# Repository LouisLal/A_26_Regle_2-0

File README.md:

# C3I A26_Règle_PCB

Compétition de Conception de Circuits Imprimés – Université de Sherbrooke, Automne 2026

## Thème : Règle PCB

Bienvenue à la compétition de conception de PCB de l’Université de Sherbrooke, édition Automne 2026!
Cette compétition a pour but d'agir comme une introduction au monde de la conception de circuit imprimé (PCB). Le thème simple de cette compétition invite les participants à expérimenter, à découvrir et à essayer quelque chose de nouveau. Votre but sera de faire un PCB qui prendra la forme d'une règle tout en ayant un circuit fonctionnel.

---

## Déroulement

Voici l'ensemble des dates importantes de la session, réparties entre les événements et les dates de commandes :

### Calendrier des événements et ateliers

* **9 septembre 2026 (17h00)** : Présentation du projet C3I A26 + Atelier de soudure THT
* **16 septembre 2026 (17h00)** : Atelier de soudure THT + Atelier d'intro à l'électronique
* **23 septembre 2026 (17h00)** : Atelier introduction à KiCad
* **30 septembre 2026 (17h00)** : Atelier Kicad - PCB
* **7 octobre 2026 (17h00)** : Séminaire - Introduction MCU
* **14 octobre 2026 (17h00)** : Séminaires sur les normes de conception électroniques (Schémas + PCB)
* **21 octobre 2026 (17h00)** : Séminaire sur les protocoles de communications
* **28 octobre 2026 (17h00)** : Atelier - Un projet sans devboards
* **4 novembre 2026 (17h00)** : Atelier de soudure (THT + SMD)
* **11 novembre 2026 (17h00)** : Période de travail et d'échange (validation par les pairs)
* **18 novembre 2026 (17h00)** : Séminaire - Intro AmpliOp
* **25 novembre 2026 (17h00)** : Atelier - MicroPython
* **2 décembre 2026 (17h00)** : Séminaire - Assemblage automatique
* **9 décembre 2026 (17h00)** : Période de travail et d'échange (validation par les pairs)
* **16 décembre 2026 (17h00)** : Période de travail et d'échange (validation par les pairs)

### Dates de commande (Pièces et PCB)

* **9 septembre 2026** : Début de la compétition
* **2 octobre 2026** : C3I - Commande de pièces ou PCB
* **16 octobre 2026** : C3I - Commande de pièces ou PCB et fin des inscriptions
* **30 octobre 2026** : C3I - Commande de pièces ou PCB
* **13 novembre 2026** : C3I - Commande de pièces ou PCB (Dernière commande LCSC)
* **27 novembre 2026** : C3I - Commande de pièces ou PCB
* **11 décembre 2026** : C3I - Commande de pièces ou PCB (Dernière commande)
* **30 décembre 2026 (23h59)** : Date limite - Remise projet C3I A26
* **4 janvier 2027 (17h30)** : Événement de compétition C3I A26 (Évaluation, présentation et remise des prix)

---

### Comment forker le dépôt

1. Accédez au dépôt GitHub officiel à l'adresse suivante : `[https://github.com/CCI-udes/A26_Regle_PCB](https://github.com/CCI-udes/A_26_Regle_2-0)`
2. Cliquez sur le bouton "Fork" en haut à droite de la page du dépôt.
3. Sélectionnez votre propre compte GitHub comme destination du fork.
4. Clonez le dépôt forké sur votre machine locale.

---

## Règlement

* Équipes de 1 à 3 personnes. **Si c'est votre première fois à faire un PCB, on vous recommande de vous mettre en équipe de 2**.
* Frais de participation : 1 e-mail à envoyer à un potentiel commanditaire par membre de l'équipe. Voir le lien suivant pour de l'aide: [Repo commandite](https://github.com/CCI-udes/documents_sponsors).
* Dimensions maximales PCB : Longueur de **15,5 cm par 3 cm maximum**.
* Les PCB ayant plus de 2 couches sont acceptés, mais la différence de prix devra être ajoutée au BOM.
* BOM maximum (produit final) : **50 $**.
* Coût de développement maximal autorisé : **100 $**.
* Utilisation de **DevBoard permise** pour le développement (pénalité de -7 points si présente dans la version finale).
* Objectif : **s’amuser et apprendre** !

---

## Remise

Chaque équipe doit fournir via son fork GitHub avant le **30 décembre 2026** :

* Schéma électrique (nettoyé et en PDF).
* Fichiers Gerber du PCB.
* Le code logiciel si applicable.
* BOM (Bill of Materials) conforme (incluant distributeurs et prix réels).
* Documentation complète du projet.

---

## Évaluation

Les projets seront notés sur un total de **250 points**, répartis de la façon suivante :

* **Idée [15 pts]** (Appréciation juges [10 pts] + Appréciation participants [5 pts])

* **Fonctionnalité [35 pts]** (Démonstration fonctionnelle [20 pts] + Compréhension des parties non-fonctionnelles [15 pts])

* **Complexité [45 pts]** (Hardware [25 pts] + Software [20 pts])

* **Gestion des ressources [25 pts]** (Bill Of Materials [20 pts] + Nombre de commandes [5 pts])

* **Démonstration [55 pts]** (Présentation orale [25 pts], Documentation écrite [20 pts], Esthétique/boîtier [10 pts])

* **Conception électronique [75 pts]** (Choix composants [10 pts], Schéma [10 pts], Qualité PCB [20 pts], Conception préventive [10 pts], Assemblage/réparation [10 pts], Qualité des soudures [15 pts])

---

## Prix

* 🏆 **Prix de conception** – Évalué sur **250 pts** (Innovation, ingéniosité, minutie et originalité dans la conception).
* ⚡ **Prix du gningnégnieur** – Évalué sur **170 pts** (Démontre une compréhension des parties non-fonctionnelles, valorise la créativité et l'apprentissage).
* 💼 **Prix du vendeur** – Évalué sur **125 pts** (Savoir organiser ses ressources, minimiser les pertes, attention au détail, esthétique et finition "best-seller").

---

## Ressources utiles

* **Microcontrôleurs recommandés** : ESP32-C3, ESP32-S3, RP2040, PB-03, CH32V003.
* **Logiciels de conception** : KiCad, Altium Designer, EasyEDA.
* **Discord** : [Lien d’invitation](https://discord.gg/xeSqf3N3Hw).

---

## Contacts

* **Jacob Turcotte** – Jacob.Turcotte@usherbrooke.ca (FAC. GÉNIE Robotique)
* **Miriam Caisse** – Miriam.Caisse@usherbrooke.ca (FAC. GÉNIE Électrique)
* **Jordan Gagnon** – Jordan.Gagnon@usherbrooke.ca (FAC. GÉNIE Électrique)
* **Alyson Bourque** - Alyson.Bourque@USherbrooke.ca (FAC. GÉNIE Électrique)
* **Céleste-Lyi Martel** - Celeste-Lyi.Martel@USherbrooke.ca (FAC. GÉNIE Robotique)

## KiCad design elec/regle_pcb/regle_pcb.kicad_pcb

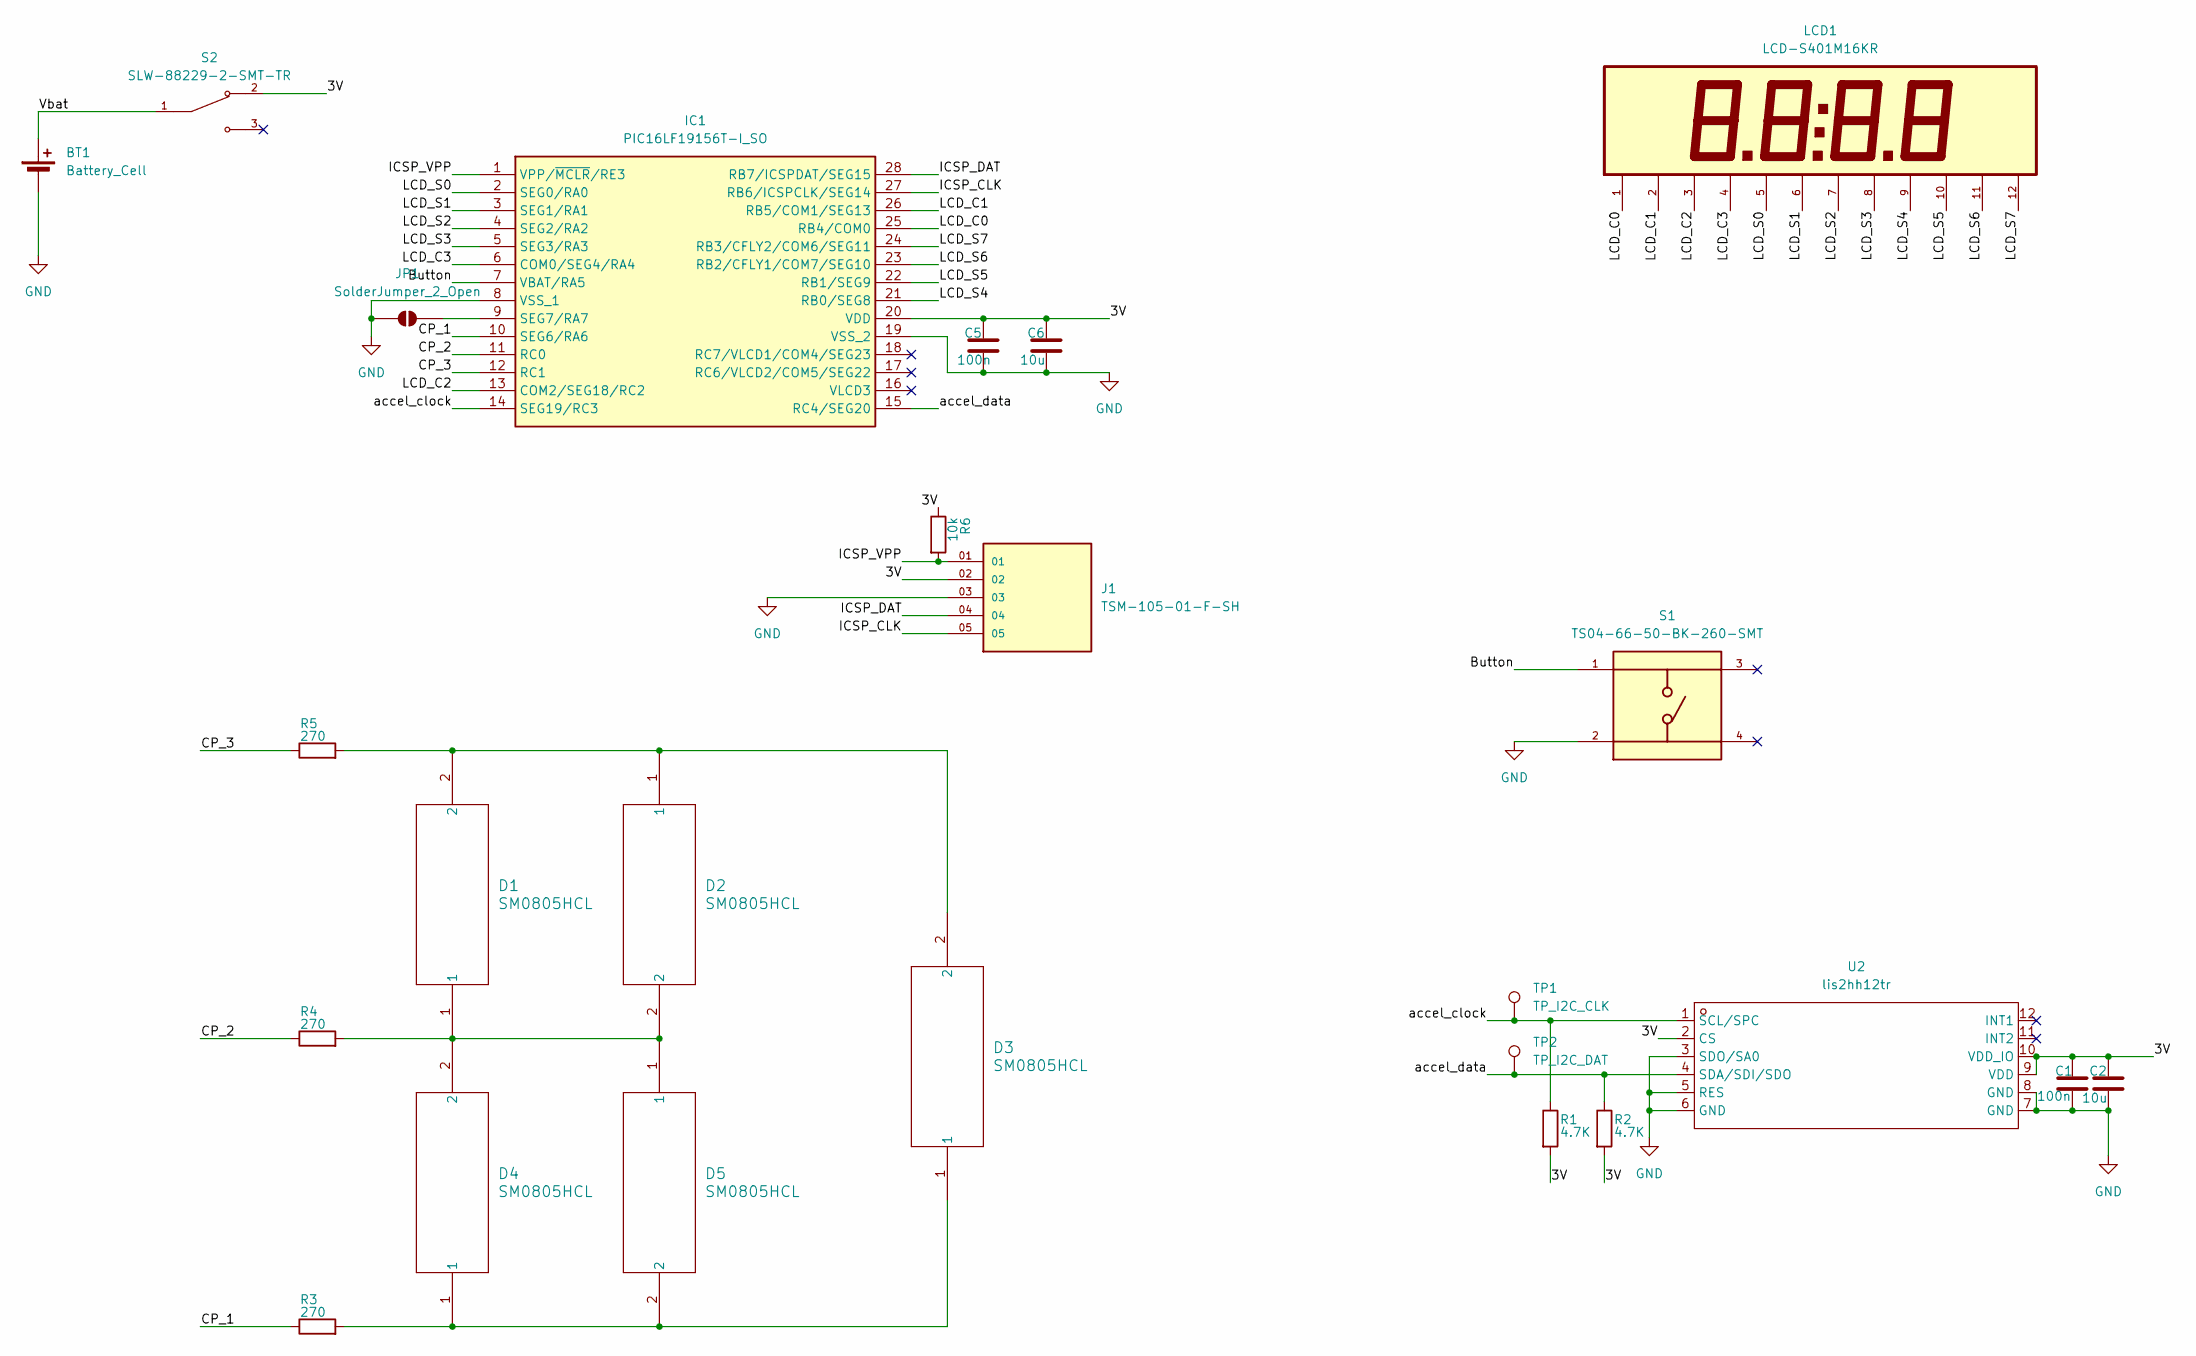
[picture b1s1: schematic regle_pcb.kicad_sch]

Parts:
BT1: Battery_Cell; BatteryHolder_Keystone_1058_1x2032
C1, C5: 100n; C_0805_2012Metric
C2, C6: 10u; C_0805_2012Metric
D1, D2, D3, D4, D5: SM0805HCL; SM0805HCL_BIV
IC1: PIC16LF19156T-I_SO; SOIC127P1030X265-28N; Manufacturer_Part_Number PIC16LF19156T-I/SO; Mouser Part Number 579-PIC16LF19156TISO
J1: TSM-105-01-F-SH; SAMTEC_TSM-105-01-F-SH; MPN TSM-105-01-F-SH
JP1: SolderJumper_2_Open; SolderJumper-2_P1.3mm_Open_TrianglePad1.0x1.5mm
LCD1: LCD-S401M16KR
R1, R2: 4.7K; R_0805_2012Metric
R3, R4, R5: 270; R_0805_2012Metric
R6: 10k; R_0805_2012Metric
S1: TS04-66-50-BK-260-SMT; SW_TS04-66-50-BK-260-SMT; MPN TS04-66-50-BK-260-SMT
S2: SLW-88229-2-SMT-TR; SW_SLW-865144-2A-N-SMT-TR; MPN SLW-88229-2-SMT-TR
TP1: TP_I2C_CLK; TestPoint_Pad_D2.0mm
TP2: TP_I2C_DAT; TestPoint_Pad_D2.0mm
U2: lis2hh12tr; PQFN50P200X200X100-12N; VOLTAGE - SUPPLY 1.71V~3.6V; MANUFACTURERPART LIS2HH12TR; LCSC PART NAME MEMS数字输出运动传感器:超低功耗高性能3轴“pico”加速度计

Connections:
/3V: C1.1, C2.1, C5.1, C6.1, IC1.20 (VDD), J1.02, R1.2, R2.2, R6.1, S2.2, U2.2 (CS), U2.9 (VDD), U2.10 (VDD_IO)
/Button: IC1.7 (VBAT/RA5), S1.1
/CP_1: IC1.10 (SEG6/RA6), R3.1
/CP_2: IC1.11 (RC0), R4.1
/CP_3: IC1.12 (RC1), R5.1
/ICSP_CLK: IC1.27 (RB6/ICSPCLK/SEG14), J1.05
/ICSP_DAT: IC1.28 (RB7/ICSPDAT/SEG15), J1.04
/ICSP_VPP: IC1.1 (VPP/~MCLR/RE3), J1.01, R6.2
/LCD_C0: IC1.25 (RB4/COM0), LCD1.1
/LCD_C1: IC1.26 (RB5/COM1/SEG13), LCD1.2
/LCD_C2: IC1.13 (COM2/SEG18/RC2), LCD1.3
/LCD_C3: IC1.6 (COM0/SEG4/RA4), LCD1.4
/LCD_S0: IC1.2 (SEG0/RA0), LCD1.5
/LCD_S1: IC1.3 (SEG1/RA1), LCD1.6
/LCD_S2: IC1.4 (SEG2/RA2), LCD1.7
/LCD_S3: IC1.5 (SEG3/RA3), LCD1.8
/LCD_S4: IC1.21 (RB0/SEG8), LCD1.9
/LCD_S5: IC1.22 (RB1/SEG9), LCD1.10
/LCD_S6: IC1.23 (RB2/CFLY1/COM7/SEG10), LCD1.11
/LCD_S7: IC1.24 (RB3/CFLY2/COM6/SEG11), LCD1.12
/Vbat: BT1.1 (+), S2.1
/accel_clock: IC1.14 (SEG19/RC3), R1.1, TP1.1 (1_1), U2.1 (SCL/SPC)
/accel_data: IC1.15 (RC4/SEG20), R2.1, TP2.1 (1_1), U2.4 (SDA/SDI/SDO)
GND: BT1.2 (-), C1.2, C2.2, C5.2, C6.2, IC1.8 (VSS_1), IC1.19 (VSS_2), J1.03, JP1.1 (A), S1.2, U2.3 (SDO/SA0), U2.5 (RES), U2.6 (GND), U2.7 (GND), U2.8 (GND)
unnamed: D1.1, D2.2, D4.2, D5.1, R4.2
unnamed: D1.2, D2.1, D3.2, R5.2
unnamed: D3.1, D4.1, D5.2, R3.2
unnamed: IC1.9 (SEG7/RA7), JP1.2 (B)

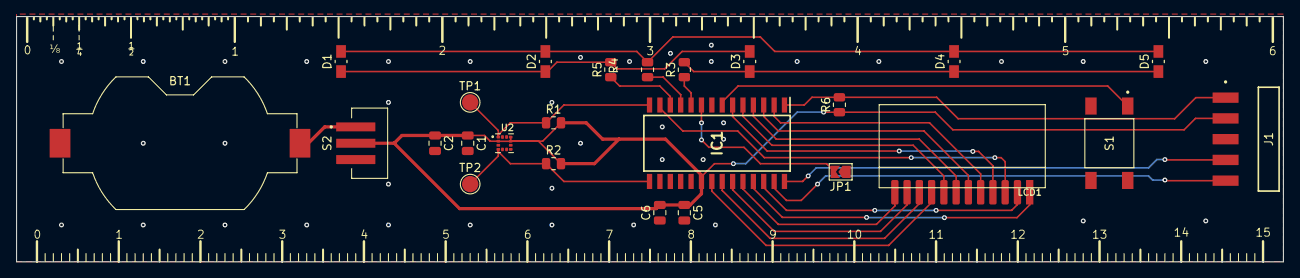
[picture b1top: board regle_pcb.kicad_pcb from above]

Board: 2 copper layers, 155.0 x 30.0 mm, 25 parts (0 on the bottom side), 28 nets.
